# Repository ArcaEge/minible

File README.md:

<div align="center">
    <h1>
        minible
    </h1>
    <p>
        <strong>
            very mini devboard with BLE and USB
        </strong>
    </p>
    <p>
        <a href="#features">features</a> •
        <a href="#pcb">PCB</a> •
        <a href="#schematics">schematics</a>
    </p>

</div>

## features

- tiny! just 8.5*9mm
- based on the nRF52833
- USB-C (full speed)
- 2 GPIOs (1 analog input)
    - P0.05, P0.11
- BLE, Thread, Matter, ANT support

## PCB

Production and BOM files are under `production/`

## schematics

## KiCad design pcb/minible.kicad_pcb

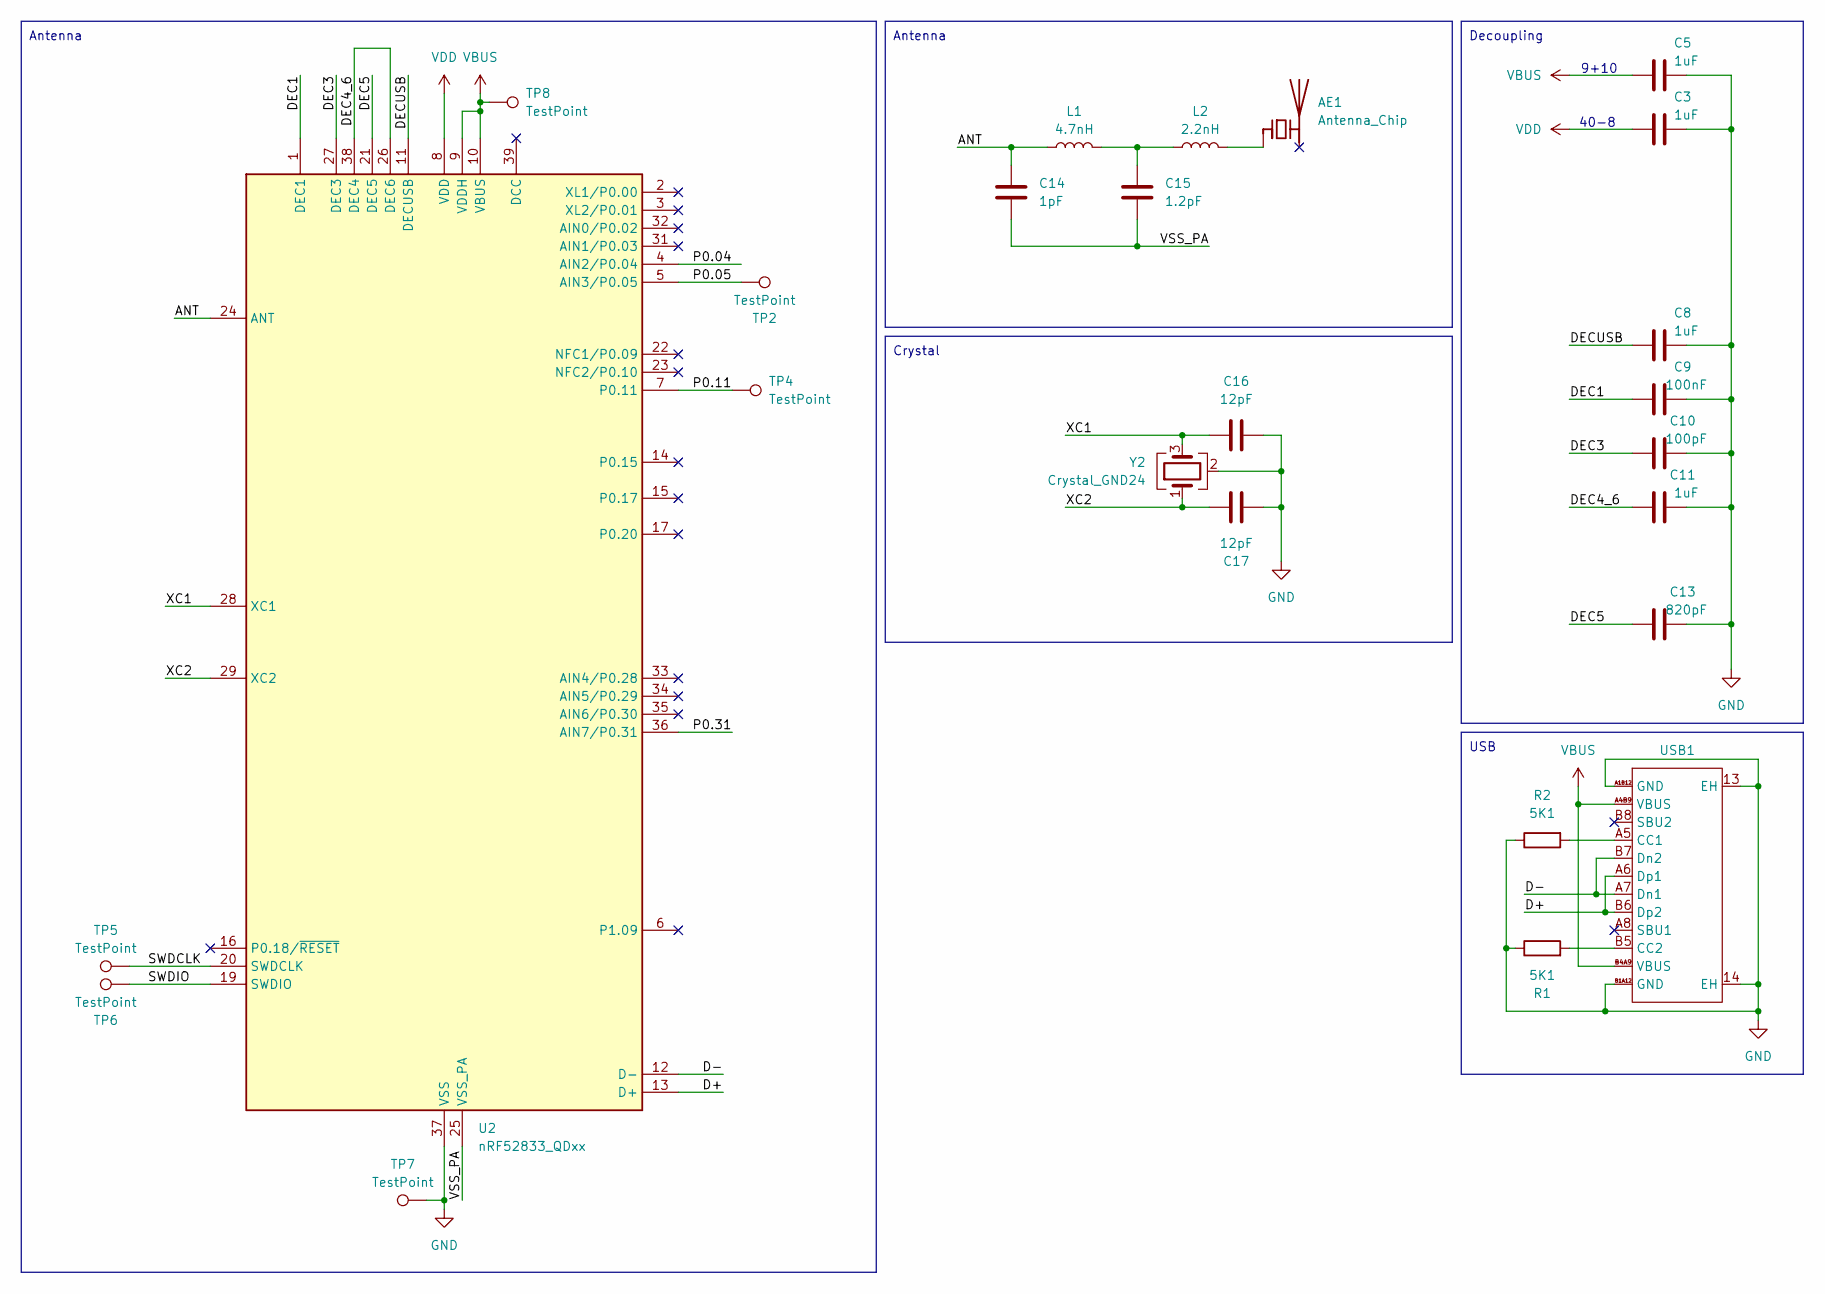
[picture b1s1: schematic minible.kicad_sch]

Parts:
AE1: Antenna_Chip; R_1206_3216Metric
C3, C5, C8, C11: 1uF; C_0201_0603Metric
C9: 100nF; C_0201_0603Metric
C10: 100pF; C_0201_0603Metric
C13: 820pF; C_0201_0603Metric
C14: 1pF; C_0201_0603Metric
C15: 1.2pF; C_0201_0603Metric
C16, C17: 12pF; C_0201_0603Metric
L1: 4.7nH; L_0201_0603Metric
L2: 2.2nH; L_0201_0603Metric
R1, R2: 5K1; R_0201_0603Metric
TP2, TP4, TP5, TP6, TP7, TP8: TestPoint; TestPoint_Keystone_5015_Micro_Mini
U2: nRF52833_QDxx; QFN-40-1EP_5x5mm_P0.4mm_EP3.6x3.6mm
USB1: USB-C-SMD_TYPE-C-16PIN-2MD-073; Manufacturer Part TYPE-C 16PIN 2MD(073); LCSC Part Name Type-C 母 卧贴
Y2: Crystal_GND24; Crystal_SMD_2016-4Pin_2.0x1.6mm

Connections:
/ANT: C14.2, L1.1, U2.24 (ANT)
/D+: U2.13 (D+), USB1.A6 (Dp1), USB1.B6 (Dp2)
/D-: U2.12 (D-), USB1.A7 (Dn1), USB1.B7 (Dn2)
/DEC1: C9.1, U2.1 (DEC1)
/DEC3: C10.1, U2.27 (DEC3)
/DEC4_6: C11.1, U2.26 (DEC6), U2.38 (DEC4)
/DEC5: C13.1, U2.21 (DEC5)
/DECUSB: C8.1, U2.11 (DECUSB)
/P0.04: U2.4 (AIN2/P0.04)
/P0.05: TP2.1 (1_1), U2.5 (AIN3/P0.05)
/P0.11: TP4.1 (1_1), U2.7 (P0.11)
/P0.31: U2.36 (AIN7/P0.31)
/SWDCLK: TP5.1 (1_1), U2.20 (SWDCLK)
/SWDIO: TP6.1 (1_1), U2.19 (SWDIO)
/VSS_PA: C14.1, C15.1, U2.25 (VSS_PA)
/XC1: C16.2, U2.28 (XC1), Y2.3
/XC2: C17.1, U2.29 (XC2), Y2.1
GND: C3.2, C5.2, C8.2, C9.2, C10.2, C11.2, C13.2, C16.1, C17.2, R1.1, R2.1, TP7.1 (1_1), U2.37 (VSS), U2.41 (VSS), USB1.13 (EH), USB1.14 (EH), USB1.A1B12 (GND), USB1.B1A12 (GND), Y2.2 (G), Y2.4 (G)
unnamed: AE1.1 (FEED_1), L2.2
unnamed: C15.2, L1.2, L2.1
unnamed: R2.2, USB1.A5 (CC1)
unnamed: R1.2, USB1.B5 (CC2)
VBUS: C5.1, TP8.1 (1_1), U2.9 (VDDH), U2.10 (VBUS), USB1.A4B9 (VBUS), USB1.B4A9 (VBUS)
VDD: C3.1, U2.8 (VDD), U2.18 (VDD), U2.30 (VDD), U2.40 (VDD)

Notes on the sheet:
40-8
Crystal
Antenna
9+10
Decoupling
USB

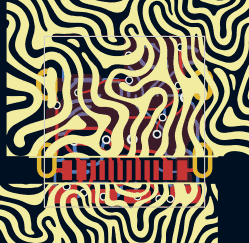
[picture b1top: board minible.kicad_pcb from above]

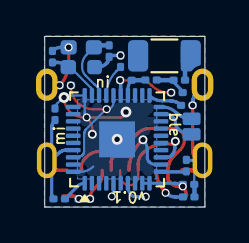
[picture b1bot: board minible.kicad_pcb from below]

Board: 2 copper layers, 8.9 x 9.5 mm, 25 parts (20 on the bottom side), 22 nets.

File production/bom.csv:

Designator,Footprint,Quantity,Value,LCSC Part #
AE1,1206,1,Antenna_Chip,
C10,0201,1,100pF,
"C11, C3, C5, C8",0201,4,1uF,
C13,0201,1,820pF,
C14,0201,1,1pF,
C15,0201,1,1.2pF,
"C16, C17",0201,2,12pF,
C9,0201,1,100nF,
L1,0201,1,4.7nH,
L2,0201,1,2.2nH,
"R1, R2",0201,2,5K1,
U2,QFN-40-1EP_5x5mm_P0.4mm_EP3.6x3.6mm,1,nRF52833_QDxx,
USB1,USB-C-SMD_TYPE-C-16PIN-2MD-073,1,~,
Y2,Crystal_SMD_2016-4Pin_2.0x1.6mm,1,Crystal_GND24,
